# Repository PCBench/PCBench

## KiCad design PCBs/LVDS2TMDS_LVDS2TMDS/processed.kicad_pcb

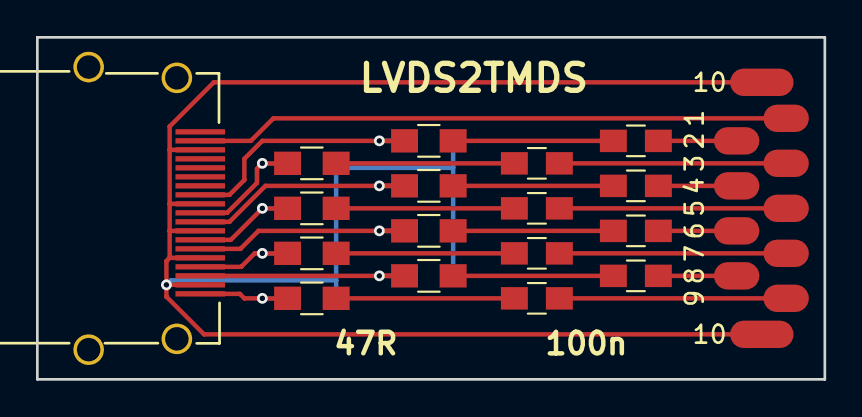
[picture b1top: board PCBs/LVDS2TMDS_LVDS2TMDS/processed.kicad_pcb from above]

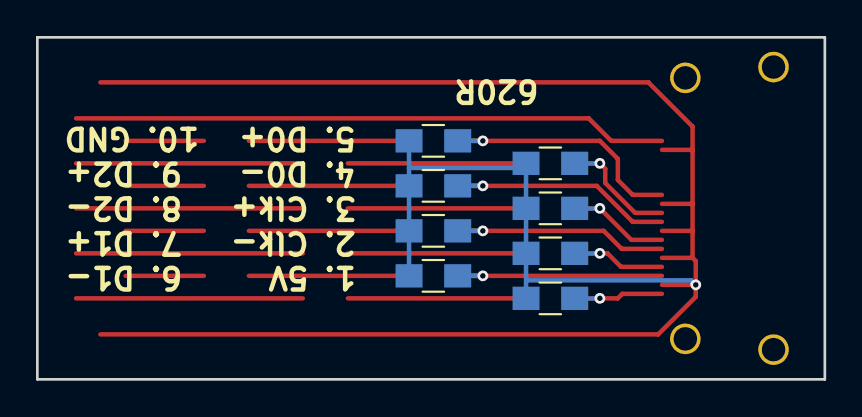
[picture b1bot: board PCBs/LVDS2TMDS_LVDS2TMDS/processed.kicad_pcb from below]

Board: 2 copper layers, 43.8 x 19.0 mm, 26 parts (8 on the bottom side), 26 nets.

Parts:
C1, C2, C3, C4, C5, C6, C7, C8: 100n; C_0805_HandSoldering
J1: HDMI; hdmi_new
P1: CONN_01X10; 10pinSolderpads
R1, R2, R5, R6, R9, R10, R13, R14: 47R; R_0805_HandSoldering
R3, R4, R7, R8, R11, R12, R15, R16: 620R; R_0805_HandSoldering

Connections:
+5V: J1.18, P1.1
GND: J1.2, J1.5, J1.8, J1.11, J1.17, P1.10, R3.1, R4.1, R7.1, R8.1, R11.1, R12.1, R15.1, R16.1
unnamed: C1.1, P1.2
unnamed: C1.2, R1.1
unnamed: C2.1, P1.3
unnamed: C2.2, R2.1
unnamed: C3.1, P1.4
unnamed: C3.2, R5.1
unnamed: C4.1, P1.5
unnamed: C4.2, R6.1
unnamed: C5.1, P1.6
unnamed: C5.2, R9.1
unnamed: C6.1, P1.7
unnamed: C6.2, R10.1
unnamed: C7.1, P1.8
unnamed: C7.2, R13.1
unnamed: C8.1, P1.9
unnamed: C8.2, R14.1
unnamed: J1.1, R14.2, R16.2
unnamed: J1.3, R13.2, R15.2
unnamed: J1.4, R10.2, R12.2
unnamed: J1.6, R9.2, R11.2
unnamed: J1.7, R6.2, R8.2
unnamed: J1.9, R5.2, R7.2
unnamed: J1.10, R2.2, R4.2
unnamed: J1.12, R1.2, R3.2

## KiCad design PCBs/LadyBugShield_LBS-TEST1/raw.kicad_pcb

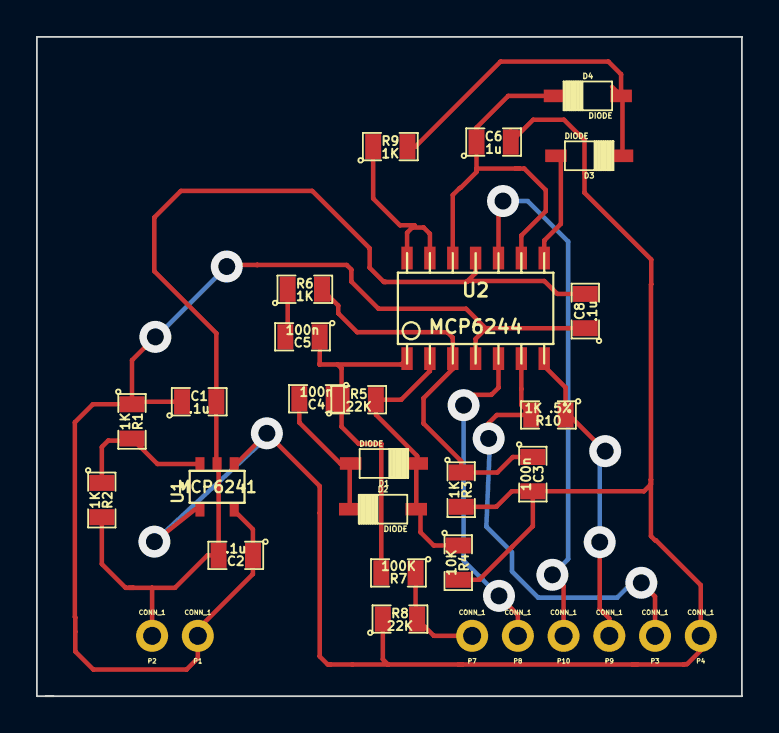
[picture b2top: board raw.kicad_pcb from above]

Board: 2 copper layers, 39.2 x 36.6 mm, 31 parts (0 on the bottom side), 18 nets.

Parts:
C1, C2, C8: .1u; SM0805
C3, C4, C5: 100n; SM0805
C6: 1u; SM0805
D1, D2, D3, D4: DIODE; SOD-123
P1, P2, P3, P4, P7, P8, P9, P10: CONN_1; LB_CONN_1
R1, R2, R3, R6, R9: 1K; SM0805
R4: 10K; SM0805
R5, R8: 22K; SM0805
R7: 100K; SM0805
R10: 1K .5%; SM0805
U1: MCP6241; SOT23-5
U2: MCP6244; LB_MCP6244

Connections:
5+V: C1.1, C2.1, C8.1, P1.1, R1.1, U1.5, U2.4
/ConvertToDigital/EC_AIN: R9.1, U2.13, U2.14
/ConvertToDigital/VGND: C3.2, C6.2, P4.1, R3.2, R4.2, R8.1, U1.1, U1.4
/GainLoop/AC_SHRUNK: P8.1, U2.5
/GainLoop/EC_ProbeIN: P3.1, R10.2, U2.6
/GainLoop/EC_SIGNAL: P9.1, R10.1, U2.7
/Rectify/DD: D3.2, D4.1, R9.2
/Rectify/EC_SIGNAL: P10.1, U2.10
/Rectify/RVin-: C6.1, D4.2, U2.9, U2.12
/Rectify/R_Vout: D3.1, U2.8
/VIn/AC_SHRUNK: P7.1, R7.1, R8.2
/VIn/G1: C4.2, D1.1, D2.2
/VIn/OSC_Vin+: C3.1, R3.1, R6.2, U2.3
/VIn/OSC_Vin-: D1.2, D2.1, R4.1, R5.2, U2.2
/VIn/OSC_Vout: C4.1, C5.1, R5.1, R7.2, U2.1
/VIn/VGND_V+: R1.2, R2.1, U1.3
/VIn/f1: C5.2, R6.1
PGND: C1.2, C2.2, C8.2, P2.1, R2.2, U1.2, U2.11

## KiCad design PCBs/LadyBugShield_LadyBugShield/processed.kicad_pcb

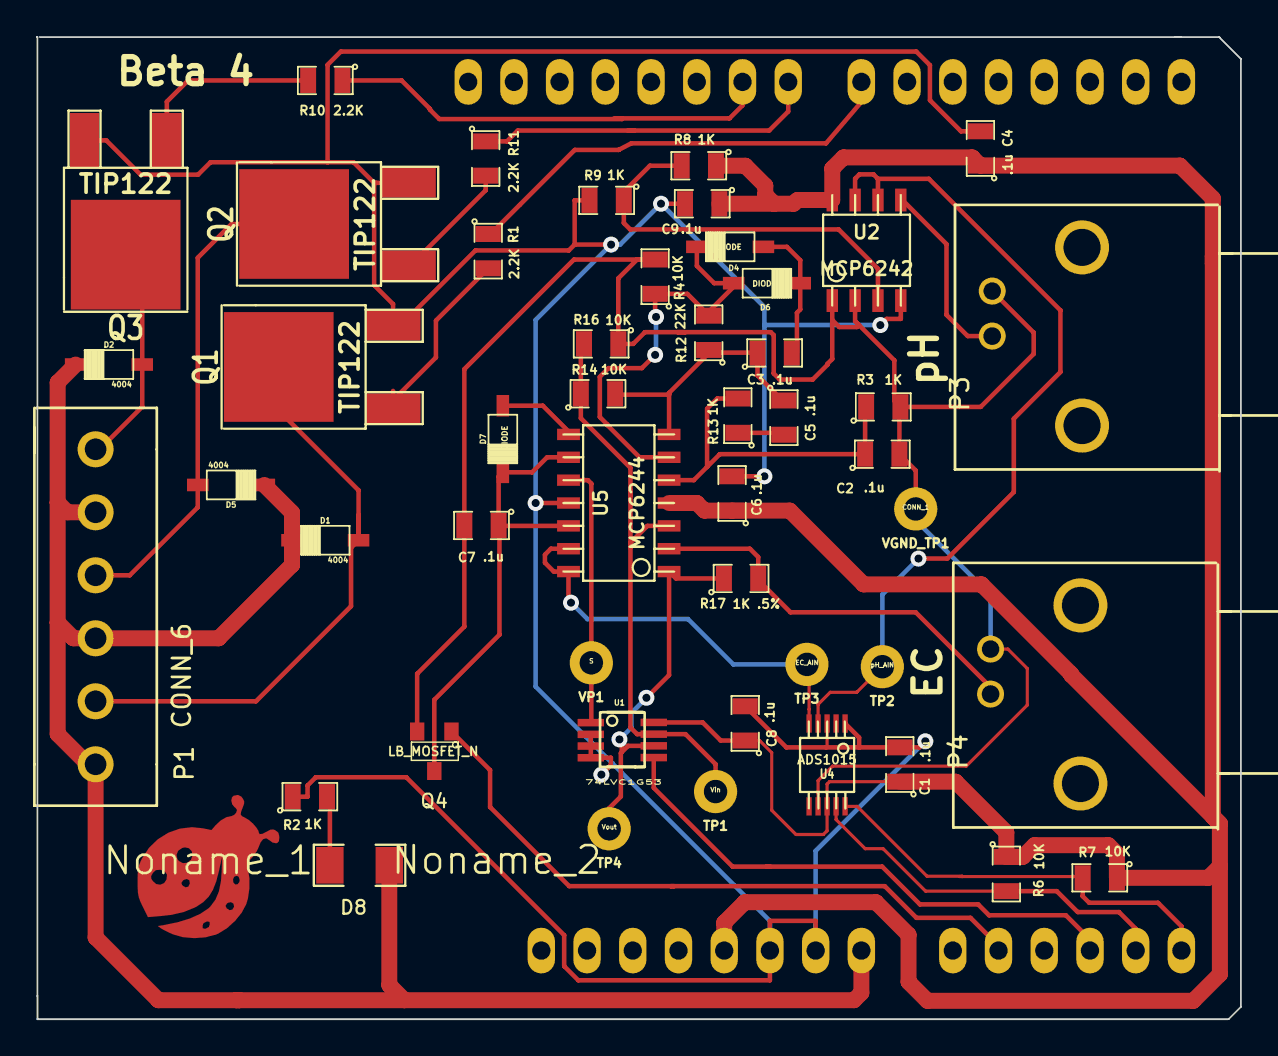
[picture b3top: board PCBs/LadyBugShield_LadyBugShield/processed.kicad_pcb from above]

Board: 2 copper layers, 66.9 x 54.6 mm, 51 parts (0 on the bottom side), 33 nets.

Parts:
ARD1: ArduinoLettuceBuddy
C1, C2, C3, C4, C5, C6, C7, C8, C9: .1u; SM0805
D1, D2, D5: 4004; SOD-123
D4, D6, D7: DIODE; SOD-123
D8: LED; SM1206
Noname_1: LadybugLogo
Noname_2: OSHW_SM
P1: CONN_6; LB_CONN_6
P3, P4: BNC; LB_BNC
Q1, Q2, Q3: TIP122; DPAK2
Q4: LB_MOSFET_N; LB_MOSFET
R1, R10, R11: 2.2K; SM0805
R2, R3, R8, R9, R13: 1K; SM0805
R4, R6, R7, R14, R16: 10K; SM0805
R12: 22K; SM0805
R17: 1K .5%; SM0805
TP1: Vin; LB_TestPoint
TP2: pH_AIN; LB_TestPoint
TP3: EC_AIN; LB_TestPoint
TP4: Vout; LB_TestPoint
U1: 74LVC1G53; LB_TSSOP8
U2: MCP6242; so-8
U4: ADS1015; msoic-10
U5: MCP6244; LB_MCP6244
VGND_TP1: CONN_1; LB_TestPoint
VP1: S; LB_TestPoint

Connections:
/Arduino/12V: ARD1.4, D1.2, D2.2, D5.2, D8.1, P1.1, P1.3, P1.5
/Arduino/FET_pin: ARD1.6, Q4.G
/Arduino/MUX_out_pin: ARD1.8, U1.5
/Arduino/SCL: ARD1.10, R7.2, U4.10
/Arduino/SDA: ARD1.9, R6.2, U4.9
/Arduino/pump1_pin: ARD1.18, R1.1
/Arduino/pump2_pin: ARD1.19, R11.1
/Arduino/pump3_pin: ARD1.20, R10.1
/DigitalAccess/EC_AIN: TP3.1, U4.5, U5.13, U5.14
/DigitalAccess/pH_AIN: TP2.1, U2.6, U2.7, U4.4
/EC/AC/EC_Vin: R14.1, R16.2, TP1.1, U1.7, U5.3
/EC/AC/G1: C3.2, D4.1, D6.2
/EC/AC/W_Vin+: C2.1, R3.1, R13.2, U5.5
/EC/AC/W_Vin-: D4.2, D6.1, R4.1, R12.2, U5.6
/EC/AC/W_Vout: C3.1, C5.1, R12.1, R14.2, U5.7
/EC/AC/f1: C5.2, R13.1
/EC/ECGain/EC_Vout: R17.1, TP4.1, U1.6, U5.1
/EC/EC_ProbeIN: P4.1, R17.2, U5.2
/EC/Rectify/RVin-: C7.1, D7.2, Q4.D, U5.9, U5.12
/EC/Rectify/R_Vout: D7.1, U5.8
/EC/Rectify/Signal: U1.1, U5.10, VP1.1
/Power/VGND_V+: R8.2, R9.1, U2.3
/Pumps/pump1: D1.1, P1.2, Q1.2
/Pumps/pump2: D5.1, P1.4, Q2.2
/Pumps/pump3: D2.1, P1.6, Q3.2
/pH/pH_ProbeIN: P3.1, U2.5
GND: ARD1.2, ARD1.3, C1.2, C4.2, C6.2, C8.2, C9.2, Q1.3, Q2.3, Q3.3, R2.1, R9.2, U1.2, U1.3, U1.4, U2.4, U4.1, U4.3, U5.11
unnamed: D8.2, R2.2
unnamed: Q1.1, R1.2
unnamed: Q2.1, R11.2
unnamed: Q3.1, R10.2
VGND: C2.2, C7.2, P3.2, P4.2, Q4.S, R3.2, R4.2, R16.1, U2.1, U2.2, U4.7, VGND_TP1.1
Vclean: ARD1.1, C1.1, C4.1, C6.1, C8.1, C9.1, R6.1, R7.1, R8.1, U1.8, U2.8, U4.8, U5.4

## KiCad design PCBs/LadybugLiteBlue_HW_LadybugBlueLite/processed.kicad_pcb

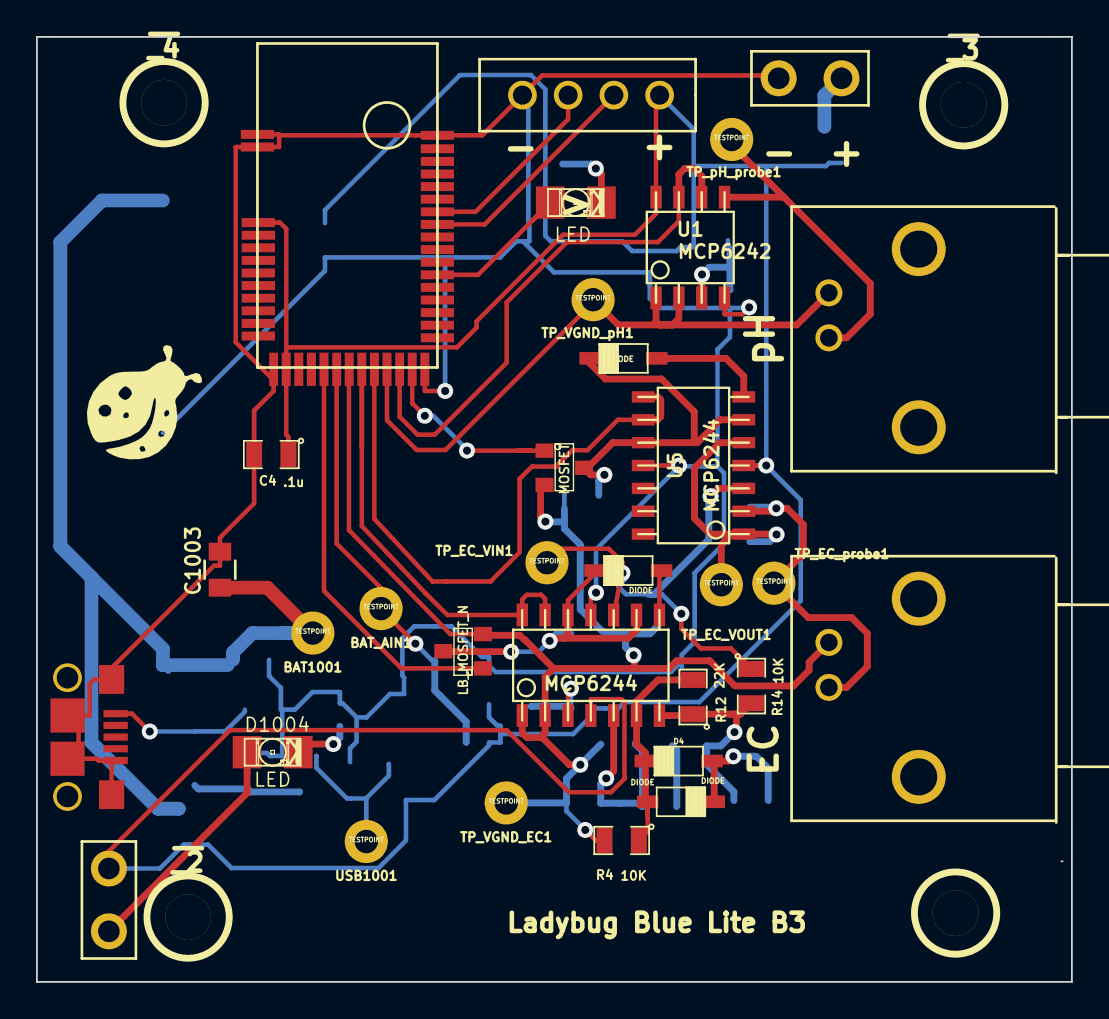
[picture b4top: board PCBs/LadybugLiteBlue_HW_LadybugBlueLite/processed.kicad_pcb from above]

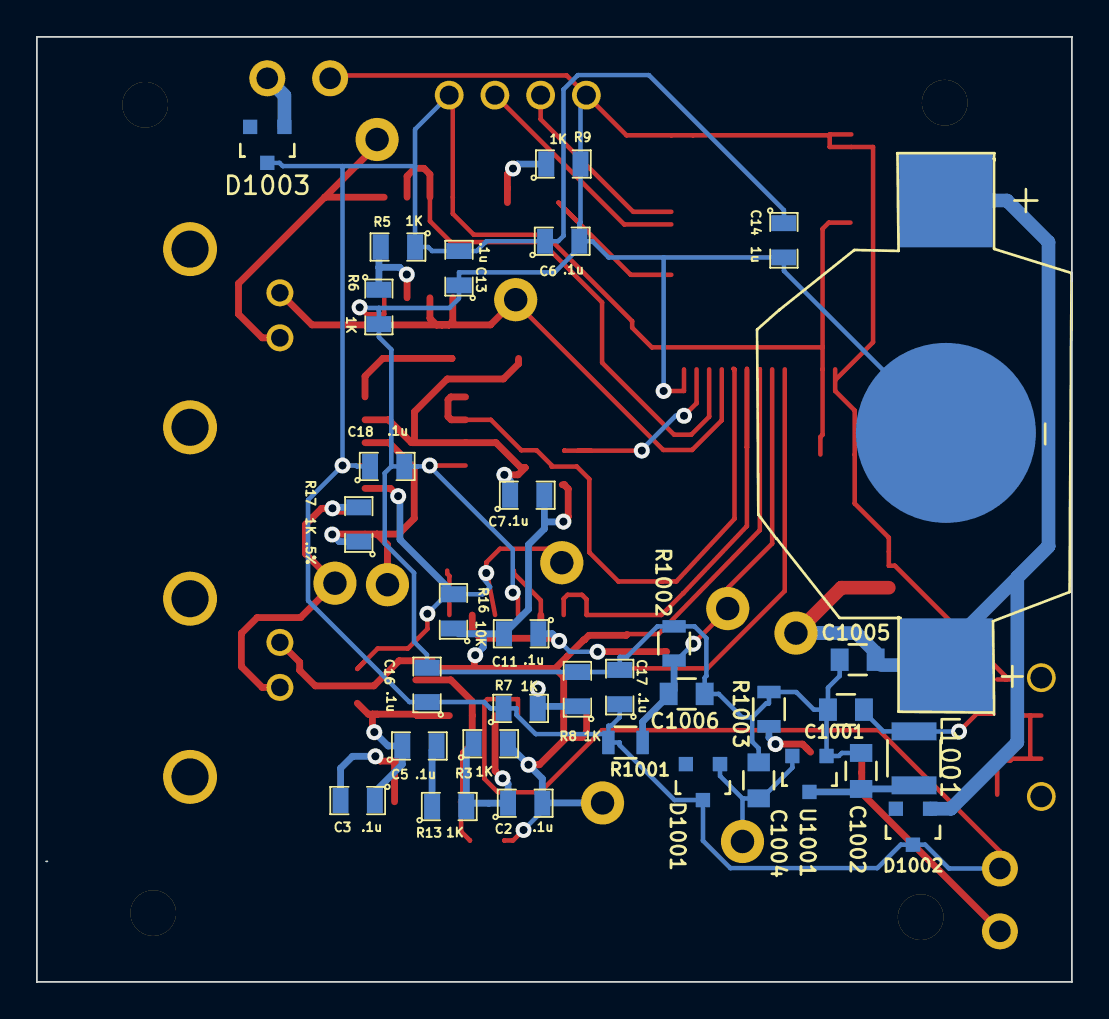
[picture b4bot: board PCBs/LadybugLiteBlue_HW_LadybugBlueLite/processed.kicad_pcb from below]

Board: 2 copper layers, 57.5 x 52.5 mm, 66 parts (34 on the bottom side), 36 nets.

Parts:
BAT1001: TESTPOINT; LB_TestPoint
BAT_AIN1: TESTPOINT; LB_TestPoint
BT1001: COIN_CELL; CR2032
C2, C3, C4, C5, C6, C7, C11, C13, C16, C17, C18: .1u; SM0805
C14: 1u; SM0805
C1001: .1u; C_0805
C1002, C1003, C1004, C1005: 10u; C_0805
C1006: 47n; C_0805
D2, D4, D6, D7: DIODE; SOD-123
D3, D1004: LED; LB_LED-1206
D1001, D1002, D1003: LB_Schottky; SOT-23
L1001: INDUCTOR; C_1210
P3: LB_HEADER_4; LB_ARDUINO_HDR_4
P4, P5: BNC; LB_BNC
P1001: USB_MICRO_B; USB-Micro-B
P1002, P1003: LB_HEADER_2; LB_CONN_2
Q1: LB_MOSFET_N; LB_MOSFET
Q4: MOSFET; LB_MOSFET
R3, R5, R6, R7, R8, R9, R13: 1K; SM0805
R4, R14, R16: 10K; SM0805
R12: 22K; SM0805
R17: 1K .5%; SM0805
R1001: 10M; R_0805
R1002: 2.2M; R_0805
R1003: 1K; R_0805
TP_EC_VIN1: TESTPOINT; LB_TestPoint
TP_EC_VOUT1: TESTPOINT; LB_TestPoint
TP_EC_probe1: TESTPOINT; LB_TestPoint
TP_VGND_EC1: TESTPOINT; LB_TestPoint
TP_VGND_pH1: TESTPOINT; LB_TestPoint
TP_pH_probe1: TESTPOINT; LB_TestPoint
U1: MCP6242; so-8
U2: MDBT40; LB_MDBT40
U4, U5: MCP6244; LB_MCP6244
U1001: MCP1700; SOT-23
USB1001: TESTPOINT; LB_TestPoint

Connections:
/nRF51822/BAT_AIN: BAT_AIN1.1, C1006.1, R1001.2, R1002.1, U2.18
/nRF51822/BLE LED: D3.1, U2.31
/nRF51822/EC_VIN_AIN: U2.20, U4.13, U4.14
/nRF51822/EC_VOUT_AIN: U2.21, U5.8, U5.9
/nRF51822/FET_VIN_pin: Q1.G, U2.17
/nRF51822/FET_VOUT_pin: Q4.G, U2.24
/nRF51822/SWCLK: P3.3, U2.36
/nRF51822/SWD: P3.2, U2.35
/nRF51822/VGND_EC: C2.2, C7.2, C11.2, P5.2, Q1.S, Q4.S, R3.2, R4.2, R16.1, TP_VGND_EC1.1, U2.19, U4.1, U4.2
/nRF51822/VGND_pH: P4.2, TP_VGND_pH1.1, U1.1, U1.2, U2.22
/nRF51822/pH_AIN: U1.6, U1.7, U2.23
/power/3V: BAT1001.1, BT1001.1, C1003.1, C1005.1, D1002.1
/power/3V3: C1004.1, D1001.1, U1001.2, USB1001.1
/power/5V: C1002.1, L1001.1, U1001.3
/power/VCC: C1001.1, L1001.2, P1001.1
/power/from_LED: D1004.2, R1003.2
/power/to_LED: D1004.1, P1003.1
/sensors/EC/AC/G1: C3.2, D4.1, D6.2
/sensors/EC/AC/W_Vin+: C2.1, R3.1, R13.2, U4.5
/sensors/EC/AC/W_Vin-: D4.2, D6.1, R4.1, R12.2, U4.6
/sensors/EC/AC/W_Vout: C3.1, C5.1, R12.1, R14.2, U4.7
/sensors/EC/AC/f1: C5.2, R13.1
/sensors/EC/Rectify/EC_VIN: R14.1, R16.2, TP_EC_VIN1.1, U4.10, U5.3
/sensors/EC/Rectify/R_VIN_-: C11.1, D2.2, Q1.D, U4.9, U4.12
/sensors/EC/Rectify/R_VIN_out: D2.1, U4.8
/sensors/EC/Rectify_VOUT/EC_VOUT: R17.1, TP_EC_VOUT1.1, U5.1, U5.5
/sensors/EC/Rectify_VOUT/R_VOUT_-: C7.1, D7.2, Q4.D, U5.6, U5.10
/sensors/EC/Rectify_VOUT/R_VOUT_OUT: D7.1, U5.7
/sensors/EC_ProbeIN: P5.1, R17.2, TP_EC_probe1.1, U5.2
/sensors/pH_ProbeIN: P4.1, TP_pH_probe1.1, U1.5
GND: BT1001.2, C4.2, C6.2, C13.1, C14.2, C16.2, C17.2, C18.2, C1001.2, C1002.2, C1003.2, C1004.2, C1005.2, C1006.2, P3.4, P1001.5, P1001.6, P1001.7, P1001.8, P1001.9, P1002.1, R6.2, R8.2, R9.2, R1002.2, R1003.1, U1.4, U2.1, U2.2, U2.13, U2.25, U2.42, U4.11, U5.11, U1001.1
unnamed: D3.2, R9.1
unnamed: D1003.1, P1002.2
unnamed: R5.2, R6.1, U1.3
unnamed: R7.2, R8.1, U4.3
PWR: C4.1, C6.1, C13.2, C14.1, C16.1, C17.1, C18.1, D1001.3, D1002.3, D1003.3, P3.1, P1003.2, R5.1, R7.1, R1001.1, U1.8, U2.3, U2.14, U4.4, U5.4
